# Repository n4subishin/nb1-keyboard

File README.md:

# Nb.1

*[日本語版はこちら / Japanese version](README.ja.md)*

A 12-position programmable macropad. Every position accepts **either a Cherry MX
compatible switch or a rotary encoder** — the two share a single footprint, so
you can build it as twelve keys, twelve knobs, or any mix in between. One
firmware build covers every variant.

| | |
|---|---|
| MCU | STM32F405RGT6 (Cortex-M4F, 168 MHz, 1 MB Flash, 192 KB RAM) |
| Matrix | 3 rows × 4 columns, COL2ROW |
| Encoders | Up to 12, wired directly to GPIO |
| Connection | USB Type-C, USB 2.0 Full Speed |
| Firmware | QMK Firmware (ChibiOS) |
| Configurator | Remap / VIA |

---

## Changing the keymap

No programming required — everything happens in the browser.

1. Open https://remap-keys.app/ in **Chrome or Edge**
   (Firefox and Safari do not implement WebHID and will not connect)
2. Choose **Customize your keyboard** and connect Nb.1
3. Drag and drop keycodes onto the positions you want to change
4. Press **flash**

Click a knob to set its clockwise and counter-clockwise actions separately.

Until Nb.1 is listed in the Remap catalog, load
[`Nb1_remap_definition.json`](Nb1_remap_definition.json) into Remap first.

---

## Building the firmware

You need a working QMK environment. See the
[QMK setup guide](https://docs.qmk.fm/newbs_getting_started) if you don't have one.

```sh
git clone https://github.com/qmk/qmk_firmware.git
cd qmk_firmware
qmk setup

# Drop this repository's keyboard directory into the QMK tree
cp -r /path/to/nb1-keyboard/keyboards/nb1 keyboards/

qmk compile -kb nb1 -km via
```

Two keymaps are provided. `default` is plain QMK; `via` adds Remap/VIA support
and is what ships on the board.

### Clock configuration

Y1 is a **16 MHz** crystal. QMK's `GENERIC_STM32_F405XG` board assumes 12 MHz,
so `board.h` and `mcuconf.h` override it:

```
PFD 2 MHz -> VCO 336 MHz -> SYSCLK 168 MHz, USB 48 MHz
```

**Deleting those two files breaks USB entirely** — the USB clock would land at
64 MHz instead of the required 48 MHz, and the core would run at 224 MHz, well
past its 168 MHz limit.

### EEPROM persistence

The STM32F405 has no real EEPROM, and QMK's flash emulation does not cover this
part by default, so it would silently fall back to a RAM-backed fake EEPROM and
lose every remap on unplug. `keymaps/via/rules.mk` selects the wear-leveling
driver explicitly to prevent that. Do not remove those lines.

---

## Flashing

Two ways into the bootloader:

**Keycode** — hold position 12 (bottom right) to reach layer 1, then press
position 1. That is `QK_BOOT` in the shipped keymap.

**BOOT0 button** — unplug USB, hold the BOOT0 button on the PCB, plug USB back
in. This works even when the firmware does not boot at all.

```sh
qmk flash -kb nb1 -km via
```

---

## Hardware

| | |
|---|---|
| PCB | 96.72 × 95.00 mm, 2 layer |
| Key pitch | 19.2 mm |
| Switches | Cherry MX compatible, Kailh hotswap sockets |
| Encoders | Alps EC12E2440301 (24 detent / 24 pulse, no push switch) |
| Crystal | 16 MHz, CL = 20 pF, HC-49/S |

Full details in [`docs/SPECIFICATION.md`](docs/SPECIFICATION.md).

### Known limitations

- **No SWD header.** Debugging requires soldering directly to MCU pins 46 and 49.
- **No reset button.** Can be retrofitted by adding a tactile switch in parallel
  with C8.
- **Matrix rows pass through the J16–J17 cable.** If that cable is disconnected,
  no key responds at all while the encoders keep working. This is the first
  thing to check when keys go dead.
- **The encoders have no push switch,** so a position fitted with an encoder
  responds to rotation only.

### JTAG pins

PA15 (JTDI), PB3 (JTDO) and PB4 (NJTRST) are used for the indicator LED and for
matrix row 3 / column 1. The board is SWD-only by design; a JTAG probe will not
work.

---

## License

Based on QMK Firmware, so this project is **GPL v2**. See [`LICENSE`](LICENSE).

USB VID `0x1209` is allocated by [pid.codes](https://pid.codes/) for open source
hardware. Projects using it must be released under a recognised open source
license, which this repository satisfies.

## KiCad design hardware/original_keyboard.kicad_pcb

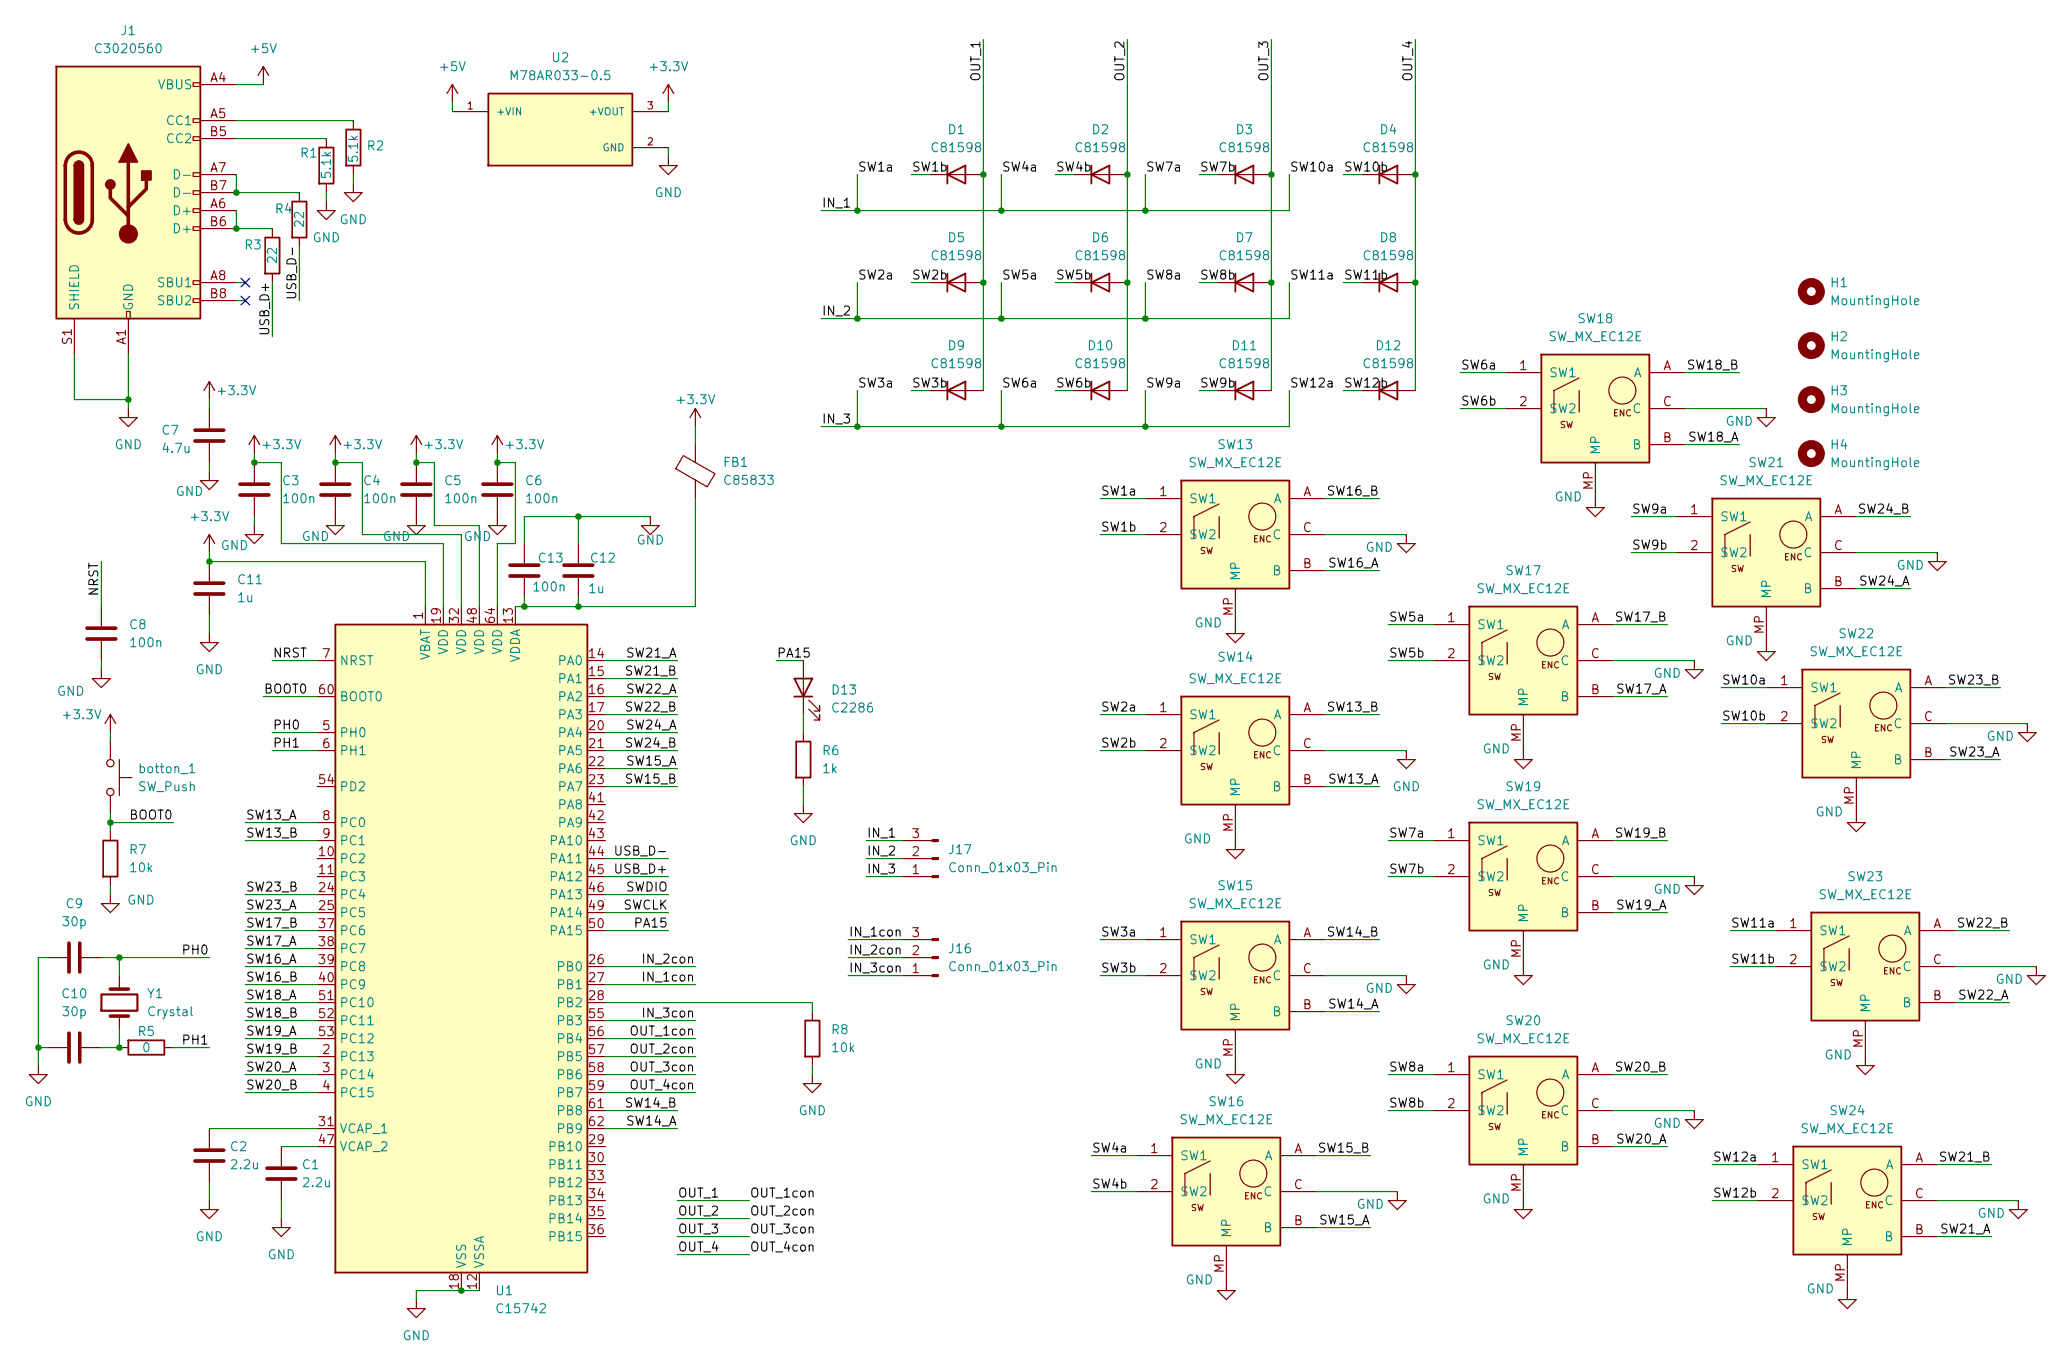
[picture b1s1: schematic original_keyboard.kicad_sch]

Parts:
C1, C2: 2.2u; C_0603_1608Metric
C3, C4, C5, C6, C8, C13: 100n; C_0603_1608Metric
C7: 4.7u; C_0603_1608Metric
C9, C10: 30p; C_0603_1608Metric
C11, C12: 1u; C_0603_1608Metric
D1, D2, D3, D4, D5, D6, D7, D8, D9, D10, D11, D12: C81598; D_SOD-123
D13: C2286; LED_0603_1608Metric
FB1: C85833; C_0603_1608Metric
H1, H2, H3, H4: MountingHole; MountingHole_3.2mm_M3
J1: C3020560; USB_C_Receptacle_GCT_USB4105-xx-A_16P_TopMnt_Horizontal
J16, J17: Conn_01x03_Pin; PinHeader_1x03_P2.54mm_Vertical
R1, R2: 5.1k; R_0603_1608Metric
R3, R4: 22; R_0603_1608Metric
R5: 0; R_0603_1608Metric
R6: 1k; R_0603_1608Metric
R7, R8: 10k; R_0603_1608Metric
SW13, SW14, SW15, SW16, SW17, SW18, SW19, SW20, SW21, SW22, SW23, SW24: SW_MX_EC12E; original1
U1: C15742; LQFP-64_10x10mm_P0.5mm
U2: M78AR033-0.5; PARTREV 4
Y1: Crystal; Crystal_HC49-U_Vertical
botton_1: SW_Push; SW_PUSH_6mm

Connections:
+3.3V: C3.1, C4.1, C5.1, C6.1, C7.1, C11.1, FB1.1, U1.1 (VBAT), U1.19 (VDD), U1.32 (VDD), U1.48 (VDD), U1.64 (VDD), U2.3 (+VOUT), botton_1.1
+5V: J1.A4 (VBUS), J1.A9 (VBUS), J1.B4 (VBUS), J1.B9 (VBUS), U2.1 (+VIN)
/BOOT0: R7.1, U1.60 (BOOT0), botton_1.2
/IN_1: J17.3, SW13.1 (SW1), SW16.1 (SW1), SW19.1 (SW1), SW22.1 (SW1)
/IN_1con: J16.3, U1.27 (PB1)
/IN_2: J17.2, SW14.1 (SW1), SW17.1 (SW1), SW20.1 (SW1), SW23.1 (SW1)
/IN_2con: J16.2, U1.26 (PB0)
/IN_3: J17.1, SW15.1 (SW1), SW18.1 (SW1), SW21.1 (SW1), SW24.1 (SW1)
/IN_3con: J16.1, U1.55 (PB3)
/NRST: C8.1, U1.7 (NRST)
/OUT_1: D1.2 (A), D5.2 (A), D9.2 (A), U1.56 (PB4)
/OUT_2: D2.2 (A), D6.2 (A), D10.2 (A), U1.57 (PB5)
/OUT_3: D3.2 (A), D7.2 (A), D11.2 (A), U1.58 (PB6)
/OUT_4: D4.2 (A), D8.2 (A), D12.2 (A), U1.59 (PB7)
/PA15: D13.2 (A), U1.50 (PA15)
/PH0: C9.1, U1.5 (PH0), Y1.2
/PH1: R5.1, U1.6 (PH1)
/SW1b: D1.1 (K), SW13.2 (SW2)
/SW2b: D5.1 (K), SW14.2 (SW2)
/SW3b: D9.1 (K), SW15.2 (SW2)
/SW4b: D2.1 (K), SW16.2 (SW2)
/SW5b: D6.1 (K), SW17.2 (SW2)
/SW6b: D10.1 (K), SW18.2 (SW2)
/SW7b: D3.1 (K), SW19.2 (SW2)
/SW8b: D7.1 (K), SW20.2 (SW2)
/SW9b: D11.1 (K), SW21.2 (SW2)
/SW10b: D4.1 (K), SW22.2 (SW2)
/SW11b: D8.1 (K), SW23.2 (SW2)
/SW12b: D12.1 (K), SW24.2 (SW2)
/SW13_A: SW14.B, U1.8 (PC0)
/SW13_B: SW14.A, U1.9 (PC1)
/SW14_A: SW15.B, U1.62 (PB9)
/SW14_B: SW15.A, U1.61 (PB8)
/SW15_A: SW16.B, U1.22 (PA6)
/SW15_B: SW16.A, U1.23 (PA7)
/SW16_A: SW13.B, U1.39 (PC8)
/SW16_B: SW13.A, U1.40 (PC9)
/SW17_A: SW17.B, U1.38 (PC7)
/SW17_B: SW17.A, U1.37 (PC6)
/SW18_A: SW18.B, U1.51 (PC10)
/SW18_B: SW18.A, U1.52 (PC11)
/SW19_A: SW19.B, U1.53 (PC12)
/SW19_B: SW19.A, U1.2 (PC13)
/SW20_A: SW20.B, U1.3 (PC14)
/SW20_B: SW20.A, U1.4 (PC15)
/SW21_A: SW24.B, U1.14 (PA0)
/SW21_B: SW24.A, U1.15 (PA1)
/SW22_A: SW23.B, U1.16 (PA2)
/SW22_B: SW23.A, U1.17 (PA3)
/SW23_A: SW22.B, U1.25 (PC5)
/SW23_B: SW22.A, U1.24 (PC4)
/SW24_A: SW21.B, U1.20 (PA4)
/SW24_B: SW21.A, U1.21 (PA5)
/SWCLK: U1.49 (PA14)
/SWDIO: U1.46 (PA13)
/USB_D+: R3.2, U1.45 (PA12)
/USB_D-: R4.2, U1.44 (PA11)
GND: C1.2, C2.2, C3.2, C4.2, C5.2, C6.2, C7.2, C8.2, C9.2, C10.2, C11.2, C12.1, C13.1, J1.A1 (GND), J1.A12 (GND), J1.B1 (GND), J1.B12 (GND), J1.S1 (SHIELD), R1.2, R2.2, R6.2, R7.2, R8.2, SW13.C, SW13.MP, SW14.C, SW14.MP, SW15.C, SW15.MP, SW16.C, SW16.MP, SW17.C, SW17.MP, SW18.C, SW18.MP, SW19.C, SW19.MP, SW20.C, SW20.MP, SW21.C, SW21.MP, SW22.C, SW22.MP, SW23.C, SW23.MP, SW24.C, SW24.MP, U1.12 (VSSA), U1.18 (VSS), U1.63 (VSS), U2.2 (GND)
unnamed: C10.1, R5.2, Y1.1
unnamed: D13.1 (K), R6.1
unnamed: J1.A5 (CC1), R2.1
unnamed: J1.B5 (CC2), R1.1
unnamed: J1.A6 (D+), J1.B6 (D+), R3.1
unnamed: J1.A7 (D-), J1.B7 (D-), R4.1
unnamed: R8.1, U1.28 (PB2)
unnamed: C2.1, U1.31 (VCAP_1)
unnamed: C1.1, U1.47 (VCAP_2)
unnamed: C12.2, C13.2, FB1.2, U1.13 (VDDA)

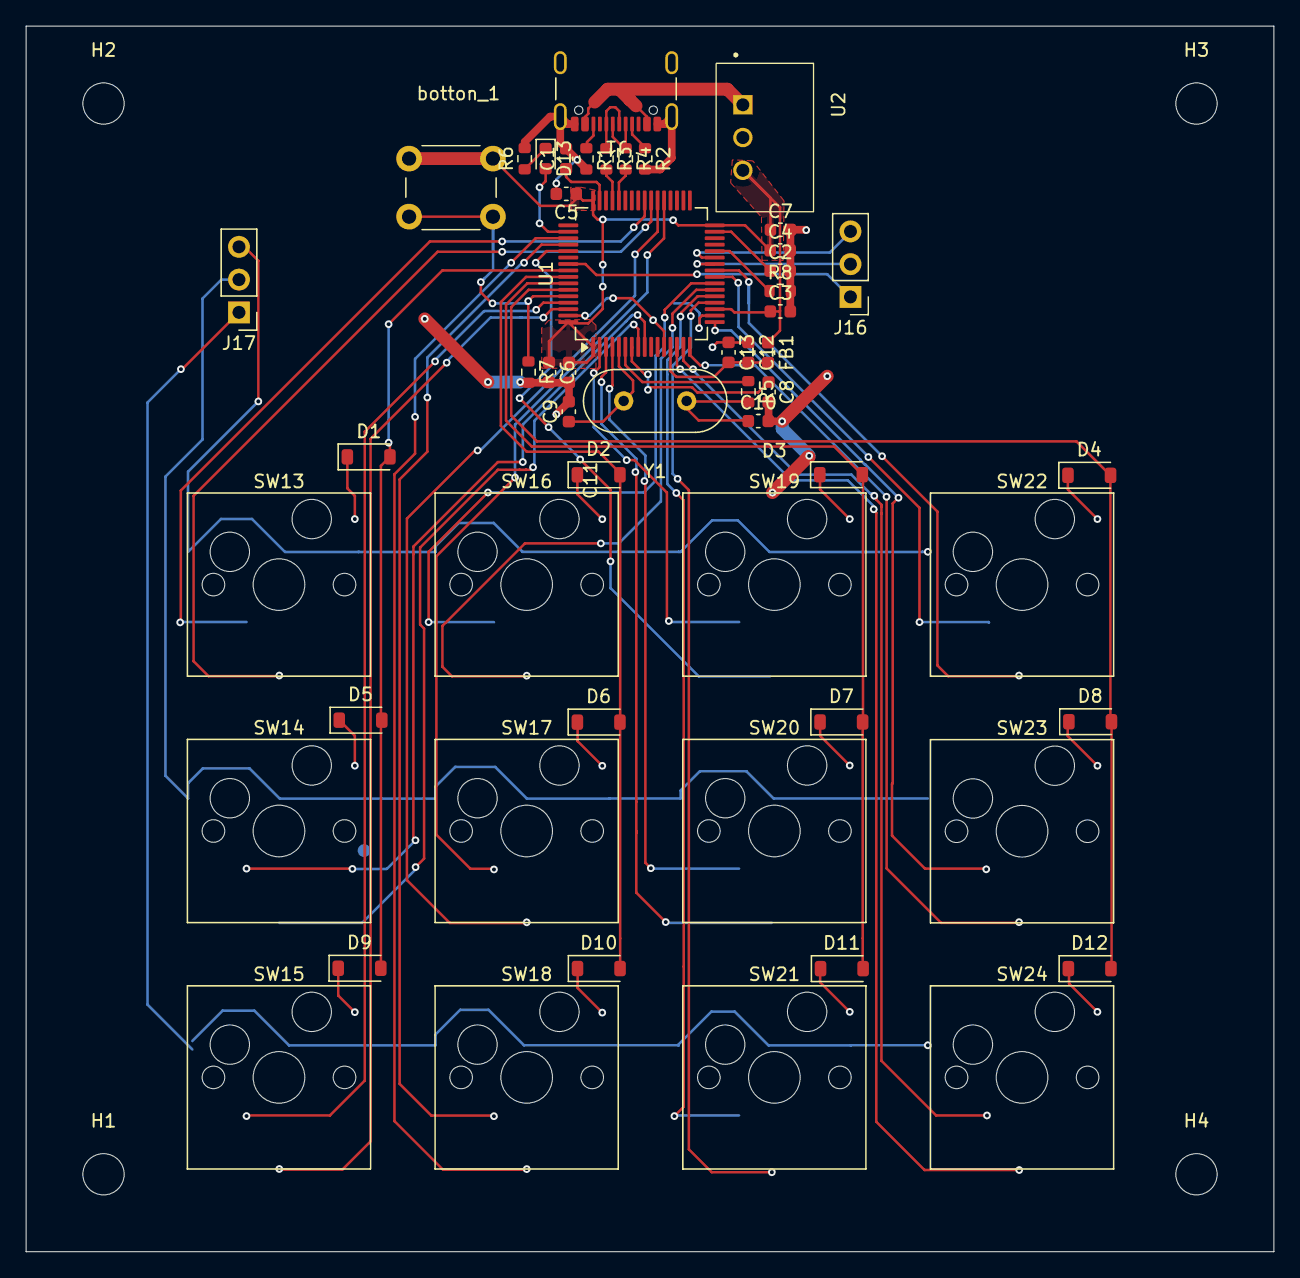
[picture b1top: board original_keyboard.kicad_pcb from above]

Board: 2 copper layers, 96.7 x 95.0 mm, 58 parts (0 on the bottom side), 66 nets.
